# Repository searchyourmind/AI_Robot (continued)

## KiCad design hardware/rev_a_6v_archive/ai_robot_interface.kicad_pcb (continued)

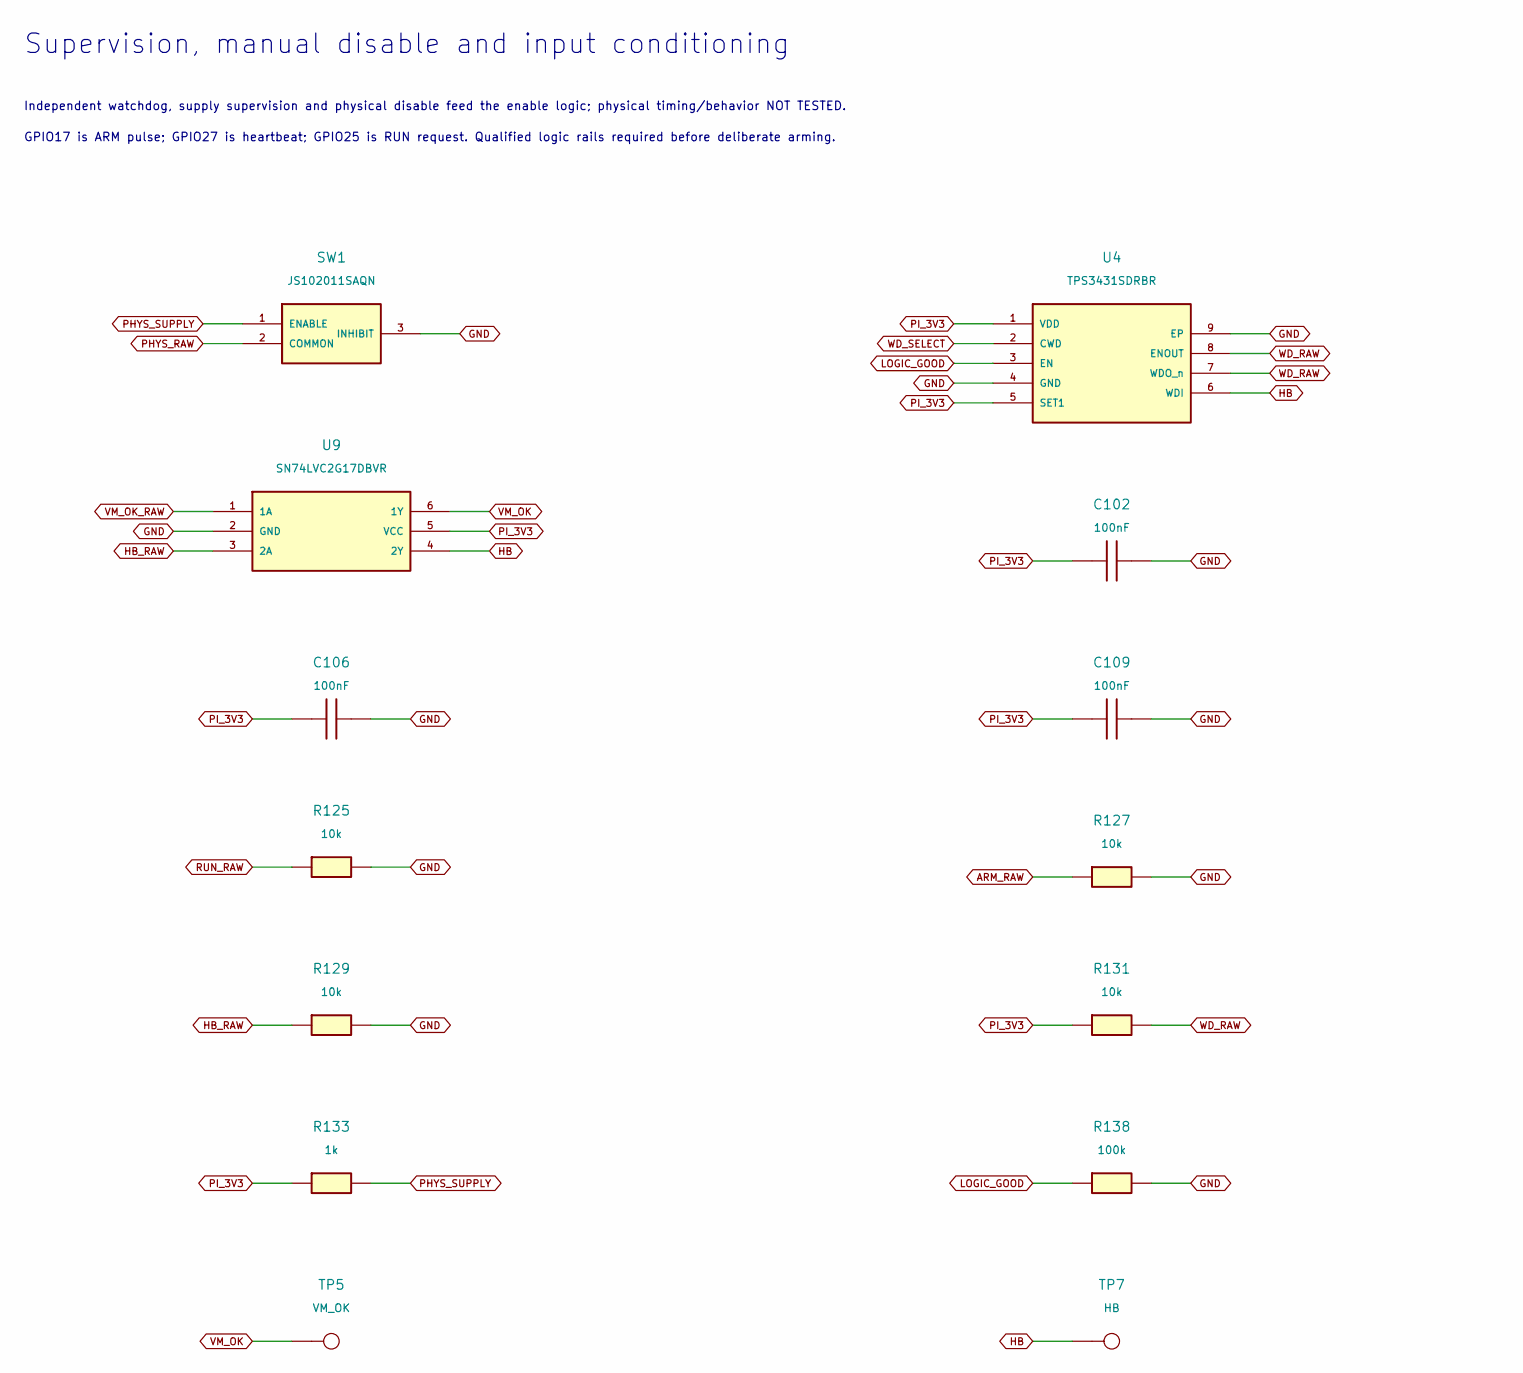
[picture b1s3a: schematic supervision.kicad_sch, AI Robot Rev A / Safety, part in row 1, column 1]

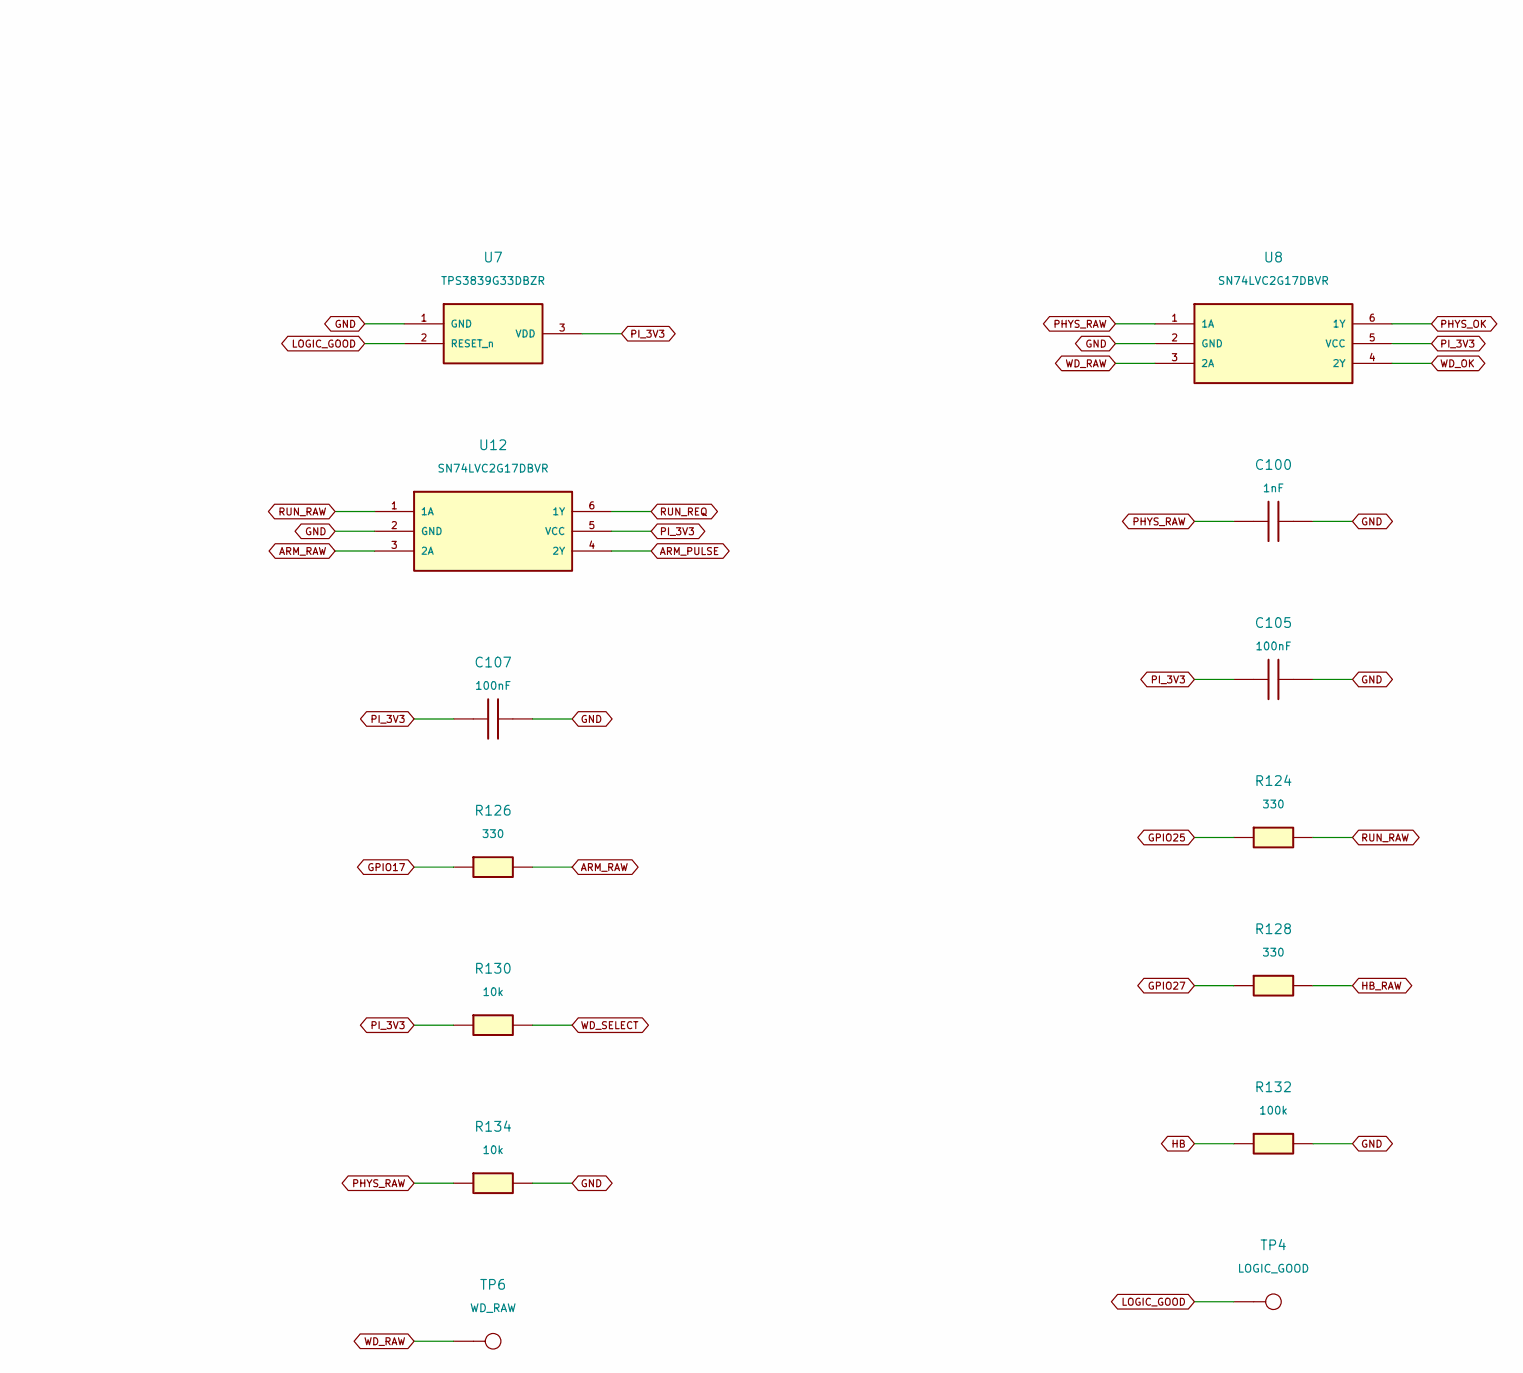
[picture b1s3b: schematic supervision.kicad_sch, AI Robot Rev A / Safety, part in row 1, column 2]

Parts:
C100: 1nF; C_0603_1608Metric; MPN GRM1885C1H102JA01D
C102, C105, C106, C107, C109: 100nF; C_0603_1608Metric; MPN CC0603KRX7R9BB104
R124, R126, R128: 330; R_0603_1608Metric; MPN RC0603FR-07330RL
R125, R127, R129, R130, R131, R134: 10k; R_0603_1608Metric; MPN RC0603FR-0710KL
R132, R138: 100k; R_0603_1608Metric; MPN RC0603FR-07100KL
R133: 1k; R_0603_1608Metric; MPN RC0603FR-071KL
SW1: JS102011SAQN; SW_SPDT_CK_JS102011SAQN; MPN JS102011SAQN
TP4: LOGIC_GOOD; TestPoint_Pad_D1.5mm; MPN PCB_COPPER_FEATURE
TP5: VM_OK; TestPoint_Pad_D1.5mm; MPN PCB_COPPER_FEATURE
TP6: WD_RAW; TestPoint_Pad_D1.5mm; MPN PCB_COPPER_FEATURE
TP7: HB; TestPoint_Pad_D1.5mm; MPN PCB_COPPER_FEATURE
U4: TPS3431SDRBR; TPS3431_DRB8_3x3_P0.65; MPN TPS3431SDRBR
U7: TPS3839G33DBZR; SOT-23; MPN TPS3839G33DBZR
U8, U9, U12: SN74LVC2G17DBVR; SOT-23-6; MPN SN74LVC2G17DBVR

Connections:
ARM_PULSE: U12.4 (2Y); also elsewhere on the board
ARM_RAW: R126.2, R127.1, U12.3 (2A)
GND: C100.2, C102.2, C105.2, C106.2, C107.2, C109.2, R125.2, R127.2, R129.2, R132.2, R134.2, R138.2, SW1.3 (INHIBIT), U4.4 (GND), U4.9 (EP), U7.1 (GND), U8.2 (GND), U9.2 (GND), U12.2 (GND); also elsewhere on the board
GPIO17: R126.1; also elsewhere on the board
GPIO25: R124.1; also elsewhere on the board
GPIO27: R128.1; also elsewhere on the board
HB: R132.1, TP7.1, U4.6 (WDI), U9.4 (2Y)
HB_RAW: R128.2, R129.1, U9.3 (2A)
LOGIC_GOOD: R138.1, TP4.1, U4.3 (EN), U7.2 (RESET_n); also elsewhere on the board
PHYS_OK: U8.6 (1Y); also elsewhere on the board
PHYS_RAW: C100.1, R134.1, SW1.2 (COMMON), U8.1 (1A)
PHYS_SUPPLY: R133.2, SW1.1 (ENABLE)
PI_3V3: C102.1, C105.1, C106.1, C107.1, C109.1, R130.1, R131.1, R133.1, U4.1 (VDD), U4.5 (SET1), U7.3 (VDD), U8.5 (VCC), U9.5 (VCC), U12.5 (VCC); also elsewhere on the board
RUN_RAW: R124.2, R125.1, U12.1 (1A)
RUN_REQ: U12.6 (1Y); also elsewhere on the board
VM_OK: TP5.1, U9.6 (1Y); also elsewhere on the board
VM_OK_RAW: U9.1 (1A); also elsewhere on the board
WD_OK: U8.4 (2Y); also elsewhere on the board
WD_RAW: R131.2, TP6.1, U4.7 (WDO_n), U4.8 (ENOUT), U8.3 (2A)
WD_SELECT: R130.2, U4.2 (CWD)

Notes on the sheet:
Supervision, manual disable and input conditioning
Independent watchdog, supply supervision and physical disable feed the enable logic; physical timing/behavior NOT TESTED.
GPIO17 is ARM pulse; GPIO27 is heartbeat; GPIO25 is RUN request. Qualified logic rails required before deliberate arming.

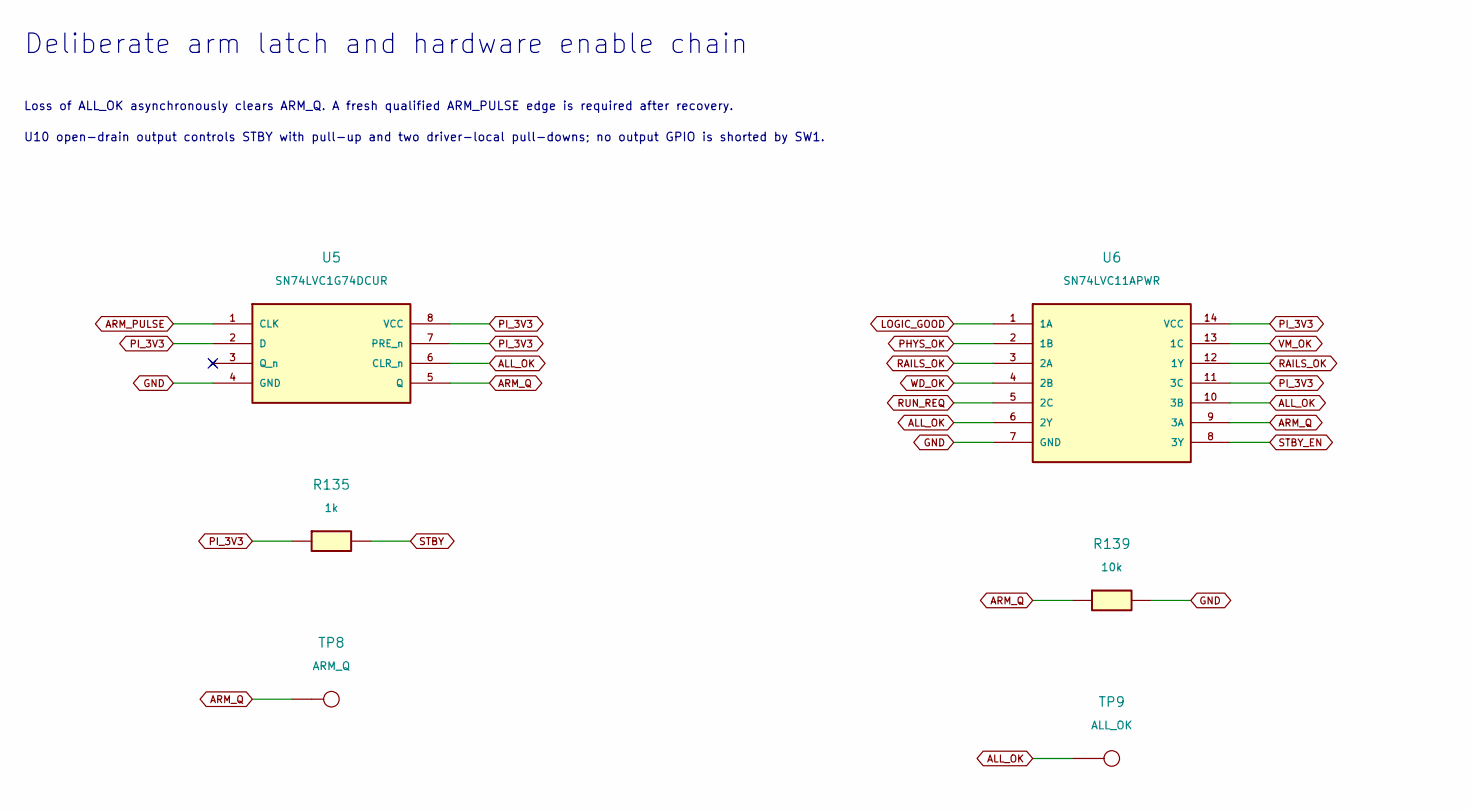
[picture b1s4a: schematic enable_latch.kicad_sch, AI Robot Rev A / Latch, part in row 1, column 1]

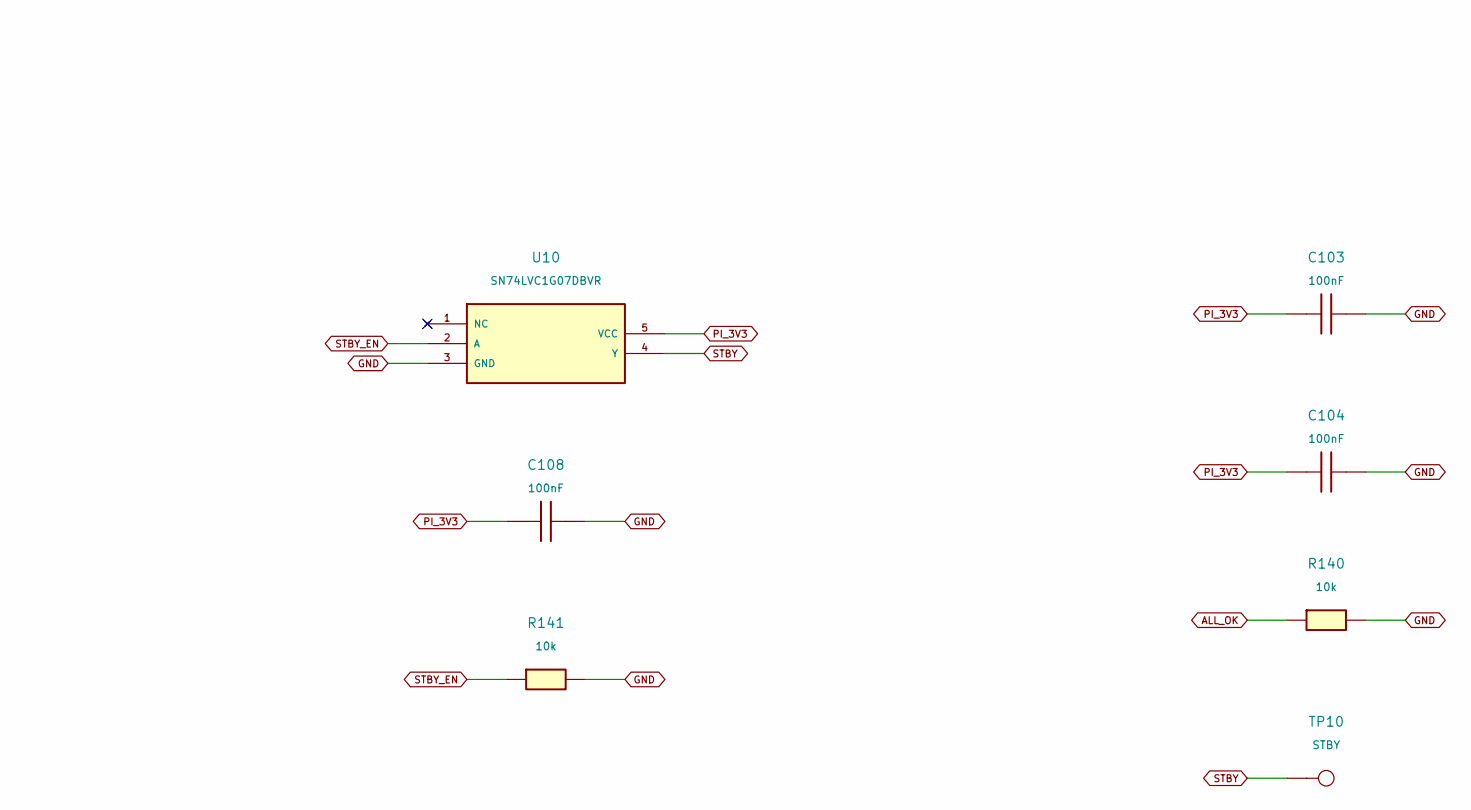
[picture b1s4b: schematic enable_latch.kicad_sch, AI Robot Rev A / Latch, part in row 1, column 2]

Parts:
C103, C104, C108: 100nF; C_0603_1608Metric; MPN CC0603KRX7R9BB104
R135: 1k; R_0603_1608Metric; MPN RC0603FR-071KL
R139, R140, R141: 10k; R_0603_1608Metric; MPN RC0603FR-0710KL
TP8: ARM_Q; TestPoint_Pad_D1.5mm; MPN PCB_COPPER_FEATURE
TP9: ALL_OK; TestPoint_Pad_D1.5mm; MPN PCB_COPPER_FEATURE
TP10: STBY; TestPoint_Pad_D1.5mm; MPN PCB_COPPER_FEATURE
U5: SN74LVC1G74DCUR; TI_DCU0008A; MPN SN74LVC1G74DCUR
U6: SN74LVC11APWR; TSSOP-14_4.4x5mm_P0.65mm; MPN SN74LVC11APWR
U10: SN74LVC1G07DBVR; SOT-23-5; MPN SN74LVC1G07DBVR

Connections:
ALL_OK: R140.1, TP9.1, U5.6 (CLR_n), U6.6 (2Y), U6.10 (3B)
ARM_PULSE: U5.1 (CLK); also elsewhere on the board
ARM_Q: R139.1, TP8.1, U5.5 (Q), U6.9 (3A)
GND: C103.2, C104.2, C108.2, R139.2, R140.2, R141.2, U5.4 (GND), U6.7 (GND), U10.3 (GND); also elsewhere on the board
LOGIC_GOOD: U6.1 (1A); also elsewhere on the board
PHYS_OK: U6.2 (1B); also elsewhere on the board
PI_3V3: C103.1, C104.1, C108.1, R135.1, U5.2 (D), U5.7 (PRE_n), U5.8 (VCC), U6.11 (3C), U6.14 (VCC), U10.5 (VCC); also elsewhere on the board
RAILS_OK: U6.3 (2A), U6.12 (1Y)
RUN_REQ: U6.5 (2C); also elsewhere on the board
STBY: R135.2, TP10.1, U10.4 (Y); also elsewhere on the board
STBY_EN: R141.1, U6.8 (3Y), U10.2 (A)
VM_OK: U6.13 (1C); also elsewhere on the board
WD_OK: U6.4 (2B); also elsewhere on the board

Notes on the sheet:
Deliberate arm latch and hardware enable chain
Loss of ALL_OK asynchronously clears ARM_Q. A fresh qualified ARM_PULSE edge is required after recovery.
U10 open-drain output controls STBY with pull-up and two driver-local pull-downs; no output GPIO is shorted by SW1.

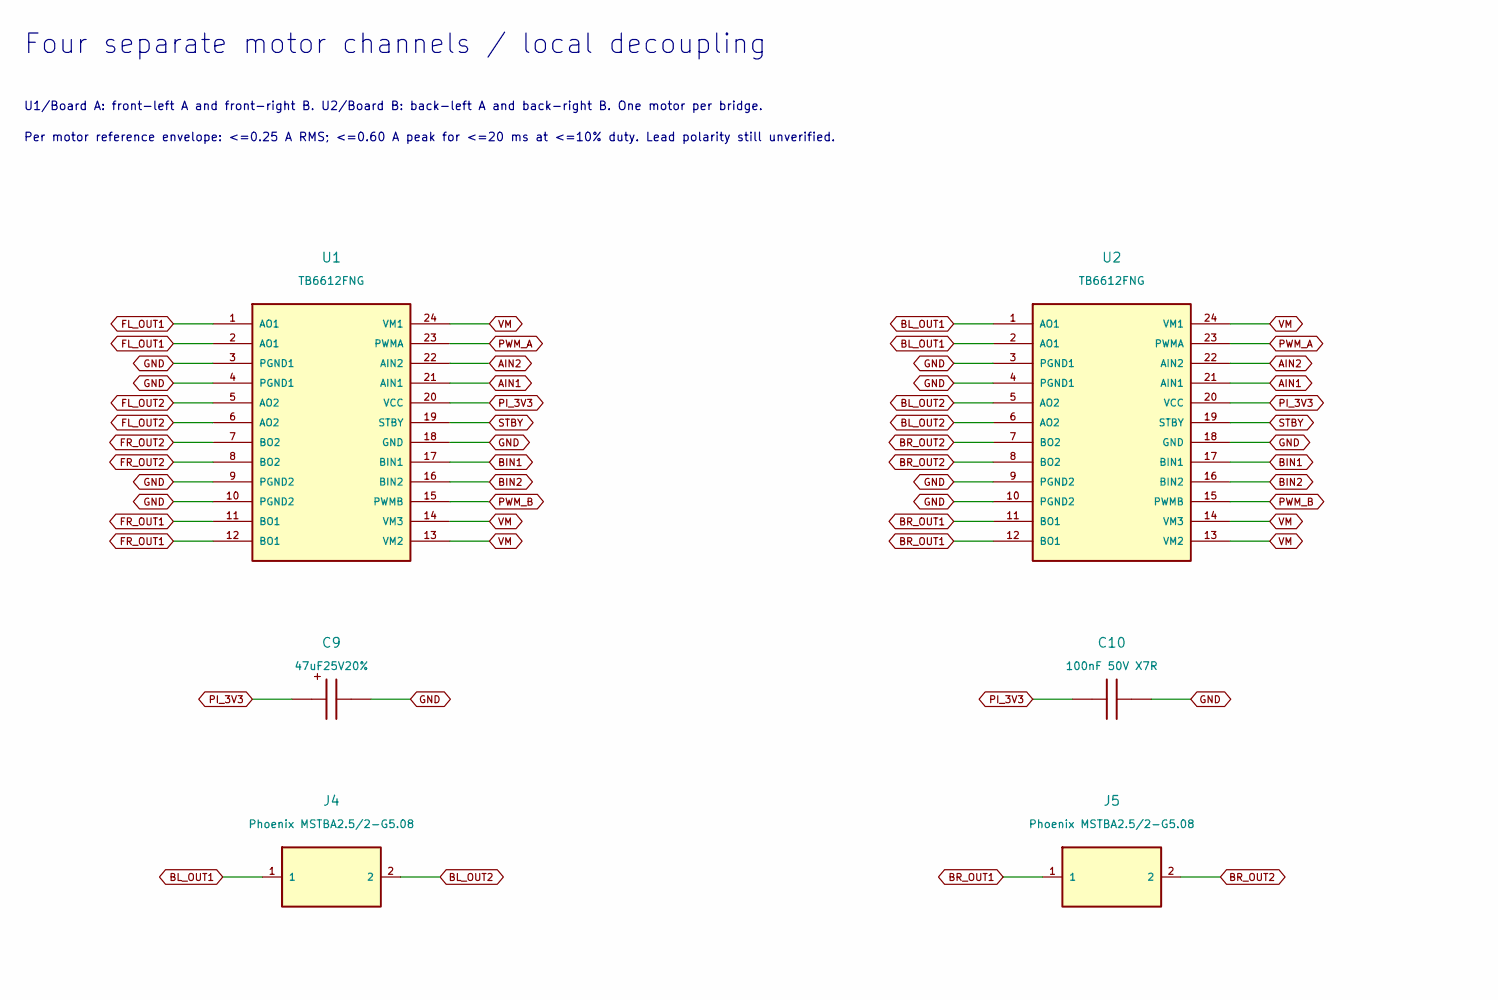
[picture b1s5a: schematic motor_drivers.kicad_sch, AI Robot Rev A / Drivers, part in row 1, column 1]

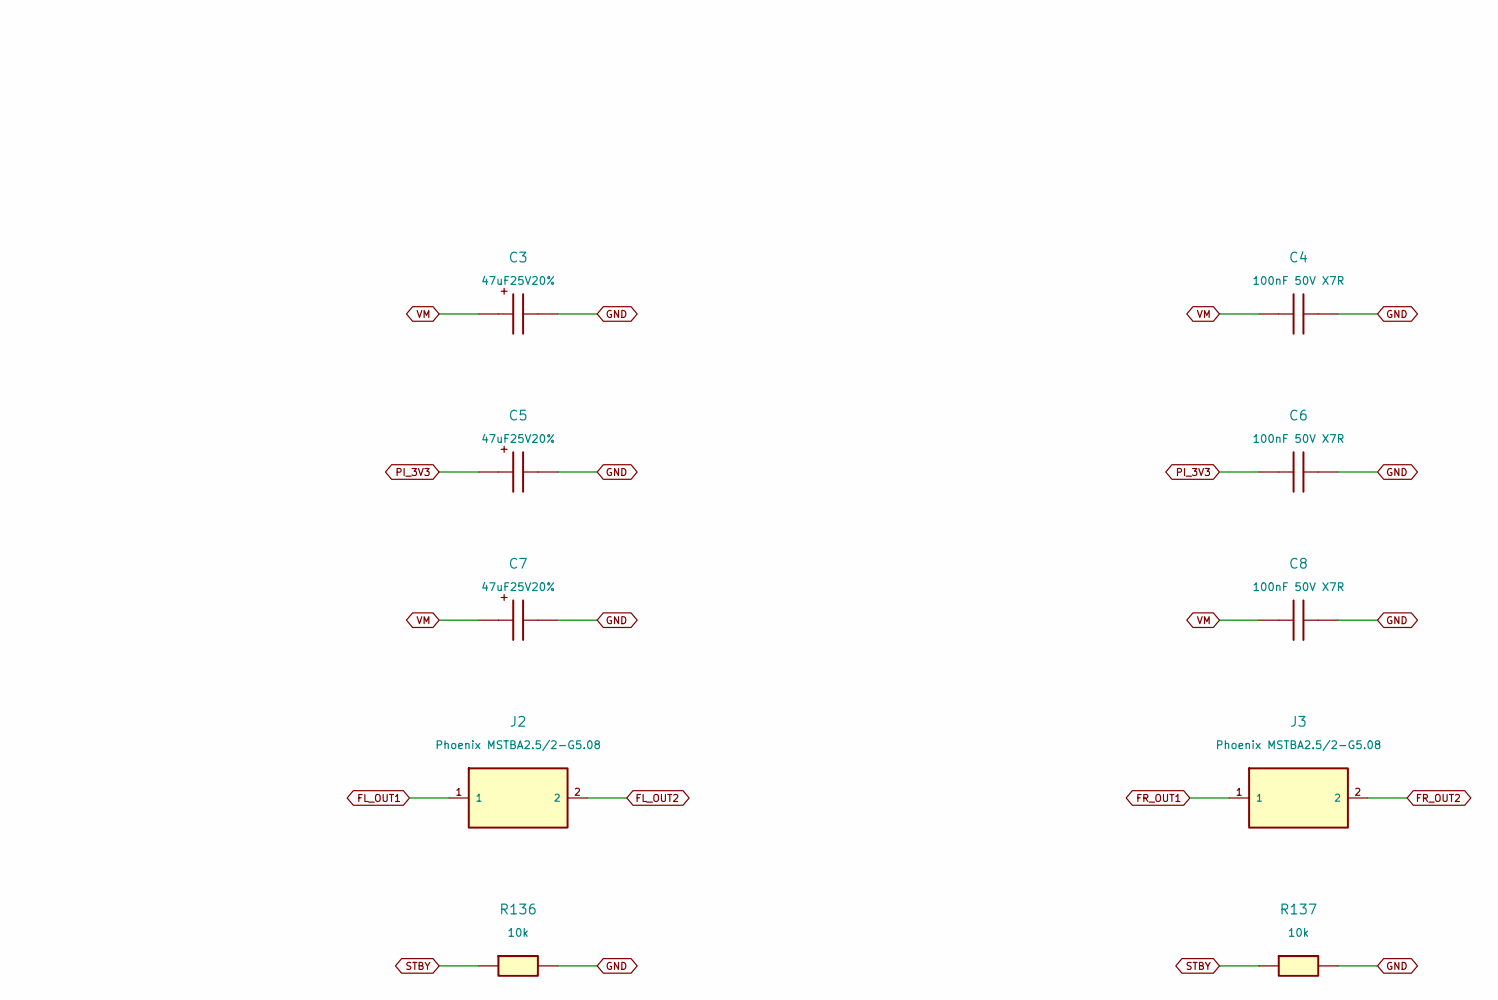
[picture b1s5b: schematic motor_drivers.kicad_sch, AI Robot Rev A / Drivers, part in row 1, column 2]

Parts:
C3, C5, C7, C9: 47uF25V20%; CP_Radial_D5.0mm_P2.00mm; MPN EEUFR1E470
C4, C6, C8, C10: 100nF 50V X7R; C_0805_2012Metric; MPN C0805C104K5RACTU
J2, J3, J4, J5: Phoenix MSTBA2.5/2-G5.08; PhoenixContact_MSTBA_2,5_2-G-5,08_1x02_P5.08mm_Horizontal; MPN 1757242
R136, R137: 10k; R_0603_1608Metric; MPN RC0603FR-0710KL
U1, U2: TB6612FNG; TB6612FNG_SSOP24_5.6x7.8_P0.65; MPN TB6612FNG(O,C,8,EL

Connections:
AIN1: U1.21 (AIN1), U2.21 (AIN1); also elsewhere on the board
AIN2: U1.22 (AIN2), U2.22 (AIN2); also elsewhere on the board
BIN1: U1.17 (BIN1), U2.17 (BIN1); also elsewhere on the board
BIN2: U1.16 (BIN2), U2.16 (BIN2); also elsewhere on the board
BL_OUT1: J4.1, U2.1 (AO1), U2.2 (AO1)
BL_OUT2: J4.2, U2.5 (AO2), U2.6 (AO2)
BR_OUT1: J5.1, U2.11 (BO1), U2.12 (BO1)
BR_OUT2: J5.2, U2.7 (BO2), U2.8 (BO2)
FL_OUT1: J2.1, U1.1 (AO1), U1.2 (AO1)
FL_OUT2: J2.2, U1.5 (AO2), U1.6 (AO2)
FR_OUT1: J3.1, U1.11 (BO1), U1.12 (BO1)
FR_OUT2: J3.2, U1.7 (BO2), U1.8 (BO2)
GND: C3.2, C4.2, C5.2, C6.2, C7.2, C8.2, C9.2, C10.2, R136.2, R137.2, U1.3 (PGND1), U1.4 (PGND1), U1.9 (PGND2), U1.10 (PGND2), U1.18 (GND), U2.3 (PGND1), U2.4 (PGND1), U2.9 (PGND2), U2.10 (PGND2), U2.18 (GND); also elsewhere on the board
PI_3V3: C5.1, C6.1, C9.1, C10.1, U1.20 (VCC), U2.20 (VCC); also elsewhere on the board
PWM_A: U1.23 (PWMA), U2.23 (PWMA); also elsewhere on the board
PWM_B: U1.15 (PWMB), U2.15 (PWMB); also elsewhere on the board
STBY: R136.1, R137.1, U1.19 (STBY), U2.19 (STBY); also elsewhere on the board
VM: C3.1, C4.1, C7.1, C8.1, U1.13 (VM2), U1.14 (VM3), U1.24 (VM1), U2.13 (VM2), U2.14 (VM3), U2.24 (VM1); also elsewhere on the board

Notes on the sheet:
Four separate motor channels / local decoupling
U1/Board A: front-left A and front-right B. U2/Board B: back-left A and back-right B. One motor per bridge.
Per motor reference envelope: <=0.25 A RMS; <=0.60 A peak for <=20 ms at <=10% duty. Lead polarity still unverified.

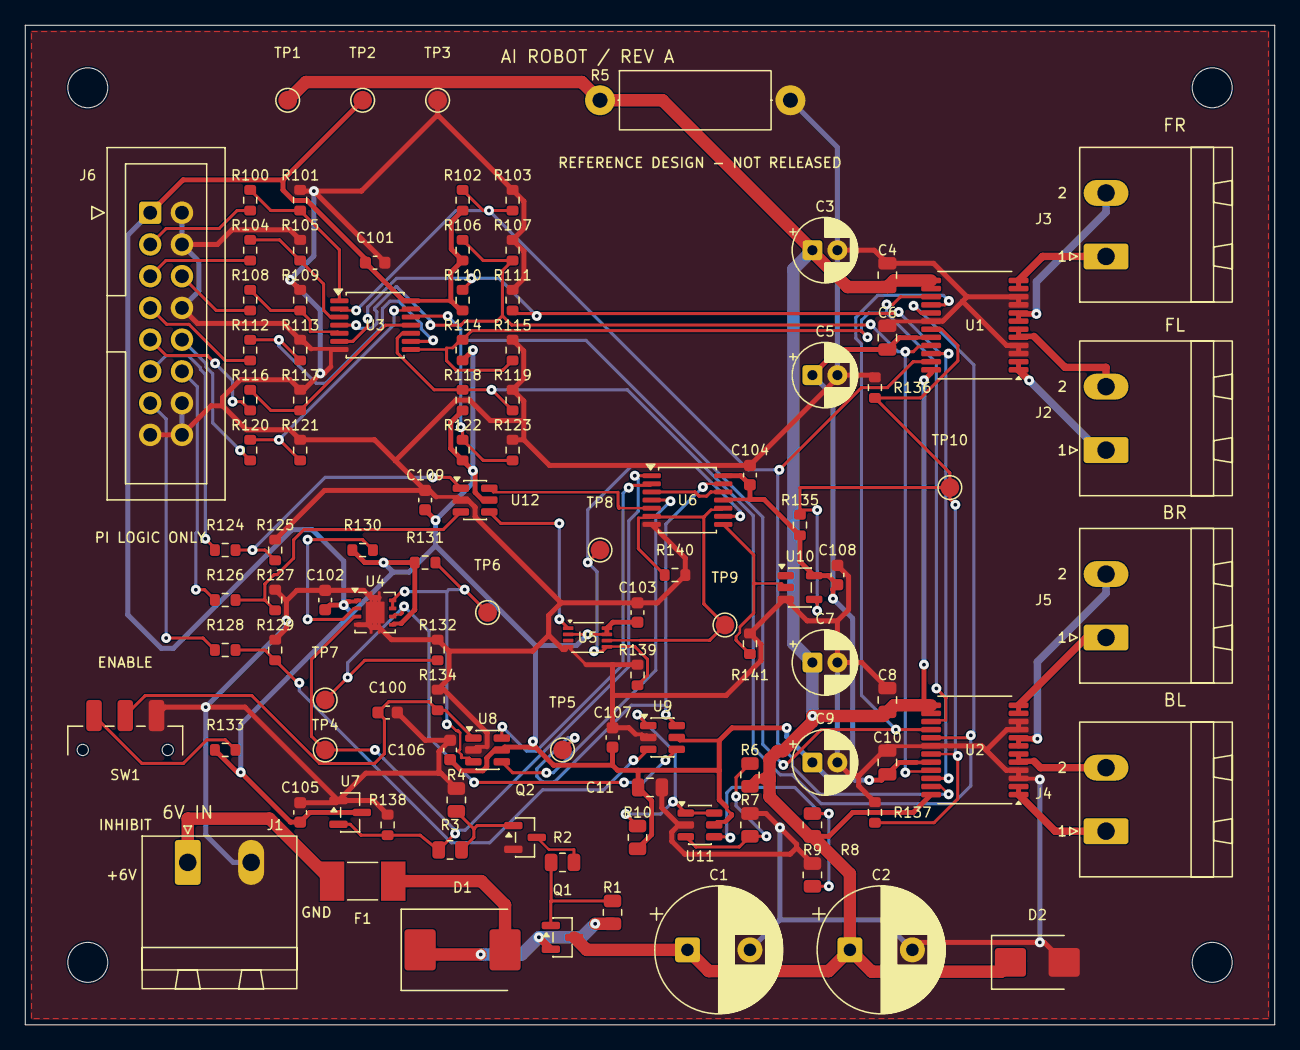
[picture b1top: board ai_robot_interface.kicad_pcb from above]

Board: 2 copper layers, 100.0 x 80.0 mm, 111 parts (0 on the bottom side), 60 nets.

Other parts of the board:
H1, H2, H3, H4: M3 NPTH; MountingHole_3.2mm_M3

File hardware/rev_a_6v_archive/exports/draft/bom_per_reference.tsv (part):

Status	References	Quantity_per_board	Manufacturer	MPN	Value	Footprint	Mount	Source_URL	Notes
DRAFT - NOT RELEASED FOR FABRICATION	C1	1	Panasonic	EEUFR1E102	1000uF25V20%	Capacitor_THT:CP_Radial_D10.0mm_P5.00mm	THT	https://industrial.panasonic.com/ww/products/pt/aluminum-cap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	1000 uF; 25 V; 20%; radial D10 x L20 mm; P5 mm
DRAFT - NOT RELEASED FOR FABRICATION	C2	1	Panasonic	EEUFR1E102	1000uF25V20%	Capacitor_THT:CP_Radial_D10.0mm_P5.00mm	THT	https://industrial.panasonic.com/ww/products/pt/aluminum-cap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	1000 uF; 25 V; 20%; radial D10 x L20 mm; P5 mm
DRAFT - NOT RELEASED FOR FABRICATION	C3	1	Panasonic	EEUFR1E470	47uF25V20%	Capacitor_THT:CP_Radial_D5.0mm_P2.00mm	THT	https://industrial.panasonic.com/ww/products/pt/aluminum-cap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	47 uF; 25 V; 20%; radial D5 x L11 mm; P2 mm
DRAFT - NOT RELEASED FOR FABRICATION	C4	1	KEMET	C0805C104K5RACTU	100nF 50V X7R	Capacitor_SMD:C_0805_2012Metric	SMD	https://search.kemet.com/download/specsheet/C0805C104K5RACTU	100 nF; 50 V; X7R; 10%; 0805
DRAFT - NOT RELEASED FOR FABRICATION	C5	1	Panasonic	EEUFR1E470	47uF25V20%	Capacitor_THT:CP_Radial_D5.0mm_P2.00mm	THT	https://industrial.panasonic.com/ww/products/pt/aluminum-cap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	47 uF; 25 V; 20%; radial D5 x L11 mm; P2 mm
DRAFT - NOT RELEASED FOR FABRICATION	C6	1	KEMET	C0805C104K5RACTU	100nF 50V X7R	Capacitor_SMD:C_0805_2012Metric	SMD	https://search.kemet.com/download/specsheet/C0805C104K5RACTU	100 nF; 50 V; X7R; 10%; 0805
DRAFT - NOT RELEASED FOR FABRICATION	C7	1	Panasonic	EEUFR1E470	47uF25V20%	Capacitor_THT:CP_Radial_D5.0mm_P2.00mm	THT	https://industrial.panasonic.com/ww/products/pt/aluminum-cap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	47 uF; 25 V; 20%; radial D5 x L11 mm; P2 mm
DRAFT - NOT RELEASED FOR FABRICATION	C8	1	KEMET	C0805C104K5RACTU	100nF 50V X7R	Capacitor_SMD:C_0805_2012Metric	SMD	https://search.kemet.com/download/specsheet/C0805C104K5RACTU	100 nF; 50 V; X7R; 10%; 0805
DRAFT - NOT RELEASED FOR FABRICATION	C9	1	Panasonic	EEUFR1E470	47uF25V20%	Capacitor_THT:CP_Radial_D5.0mm_P2.00mm	THT	https://industrial.panasonic.com/ww/products/pt/aluminum-cap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	47 uF; 25 V; 20%; radial D5 x L11 mm; P2 mm
DRAFT - NOT RELEASED FOR FABRICATION	C10	1	KEMET	C0805C104K5RACTU	100nF 50V X7R	Capacitor_SMD:C_0805_2012Metric	SMD	https://search.kemet.com/download/specsheet/C0805C104K5RACTU	100 nF; 50 V; X7R; 10%; 0805
DRAFT - NOT RELEASED FOR FABRICATION	C11	1	KEMET	C0805C104K5RACTU	100nF 50V X7R	Capacitor_SMD:C_0805_2012Metric	SMD	https://search.kemet.com/download/specsheet/C0805C104K5RACTU	100 nF; 50 V; X7R; 10%; 0805
DRAFT - NOT RELEASED FOR FABRICATION	C100	1	Murata	GRM1885C1H102JA01D	1nF	Capacitor_SMD:C_0603_1608Metric	SMD	https://datasheet.octopart.com/GRM1885C1H102JA01D-Murata-dat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	Manufacturer-authored archived datasheet; direct manufacturer retrieval unavailable; refresh before procurement; 1 nF; C0G; 50 V; 5%; 0603
DRAFT - NOT RELEASED FOR FABRICATION	C101	1	YAGEO	CC0603KRX7R9BB104	100nF	Capacitor_SMD:C_0603_1608Metric	SMD	https://yageogroup.com/download/specsheet/CC0603KRX7R9BB104	100 nF; 50 V; X7R; 10%; 0603
DRAFT - NOT RELEASED FOR FABRICATION	C102	1	YAGEO	CC0603KRX7R9BB104	100nF	Capacitor_SMD:C_0603_1608Metric	SMD	https://yageogroup.com/download/specsheet/CC0603KRX7R9BB104	100 nF; 50 V; X7R; 10%; 0603
DRAFT - NOT RELEASED FOR FABRICATION	C103	1	YAGEO	CC0603KRX7R9BB104	100nF	Capacitor_SMD:C_0603_1608Metric	SMD	https://yageogroup.com/download/specsheet/CC0603KRX7R9BB104	100 nF; 50 V; X7R; 10%; 0603
DRAFT - NOT RELEASED FOR FABRICATION	C104	1	YAGEO	CC0603KRX7R9BB104	100nF	Capacitor_SMD:C_0603_1608Metric	SMD	https://yageogroup.com/download/specsheet/CC0603KRX7R9BB104	100 nF; 50 V; X7R; 10%; 0603
DRAFT - NOT RELEASED FOR FABRICATION	C105	1	YAGEO	CC0603KRX7R9BB104	100nF	Capacitor_SMD:C_0603_1608Metric	SMD	https://yageogroup.com/download/specsheet/CC0603KRX7R9BB104	100 nF; 50 V; X7R; 10%; 0603
DRAFT - NOT RELEASED FOR FABRICATION	C106	1	YAGEO	CC0603KRX7R9BB104	100nF	Capacitor_SMD:C_0603_1608Metric	SMD	https://yageogroup.com/download/specsheet/CC0603KRX7R9BB104	100 nF; 50 V; X7R; 10%; 0603
DRAFT - NOT RELEASED FOR FABRICATION	C107	1	YAGEO	CC0603KRX7R9BB104	100nF	Capacitor_SMD:C_0603_1608Metric	SMD	https://yageogroup.com/download/specsheet/CC0603KRX7R9BB104	100 nF; 50 V; X7R; 10%; 0603
DRAFT - NOT RELEASED FOR FABRICATION	C108	1	YAGEO	CC0603KRX7R9BB104	100nF	Capacitor_SMD:C_0603_1608Metric	SMD	https://yageogroup.com/download/specsheet/CC0603KRX7R9BB104	100 nF; 50 V; X7R; 10%; 0603
DRAFT - NOT RELEASED FOR FABRICATION	C109	1	YAGEO	CC0603KRX7R9BB104	100nF	Capacitor_SMD:C_0603_1608Metric	SMD	https://yageogroup.com/download/specsheet/CC0603KRX7R9BB104	100 nF; 50 V; X7R; 10%; 0603
DRAFT - NOT RELEASED FOR FABRICATION	D1	1	Vishay	SSC54-E3/57T	40V 5A	Diode_SMD:D_SMC	SMD	https://www.vishay.com/docs/88885/ssc53l.pdf	SMC; cathode band to REV_PROTECTED
DRAFT - NOT RELEASED FOR FABRICATION	D2	1	Littelfuse	SMBJ7.0A	7V unidirectional	Diode_SMD:D_SMB	SMD	https://www.littelfuse.com/assetdocs/tvs-diodes-smbj-series-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	Unidirectional; cathode band to VM
DRAFT - NOT RELEASED FOR FABRICATION	F1	1	Littelfuse	0451002.MRL	2A 125V	AI_Robot:Fuse_Littelfuse_451	SMD	https://www.littelfuse.com/assetdocs/fuse-451-and-453-datash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	2 A; non-resettable; not a per-channel current limiter
DRAFT - NOT RELEASED FOR FABRICATION	J1	1	Phoenix Contact	1757242	Phoenix MSTBA2.5/2-G5.08	Connector_Phoenix_MSTB:PhoenixContact_MSTBA_2,5_2-G-5,08_1x02_P5.08mm_Horizontal	THT	https://www.phoenixcontact.com/en-de/products/pcb-header-mst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	Board header only; off-board mating plug 1757019 listed separately
DRAFT - NOT RELEASED FOR FABRICATION	J2	1	Phoenix Contact	1757242	Phoenix MSTBA2.5/2-G5.08	Connector_Phoenix_MSTB:PhoenixContact_MSTBA_2,5_2-G-5,08_1x02_P5.08mm_Horizontal	THT	https://www.phoenixcontact.com/en-de/products/pcb-header-mst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	Board header only; off-board mating plug 1757019 listed separately
DRAFT - NOT RELEASED FOR FABRICATION	J3	1	Phoenix Contact	1757242	Phoenix MSTBA2.5/2-G5.08	Connector_Phoenix_MSTB:PhoenixContact_MSTBA_2,5_2-G-5,08_1x02_P5.08mm_Horizontal	THT	https://www.phoenixcontact.com/en-de/products/pcb-header-mst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	Board header only; off-board mating plug 1757019 listed separately
DRAFT - NOT RELEASED FOR FABRICATION	J4	1	Phoenix Contact	1757242	Phoenix MSTBA2.5/2-G5.08	Connector_Phoenix_MSTB:PhoenixContact_MSTBA_2,5_2-G-5,08_1x02_P5.08mm_Horizontal	THT	https://www.phoenixcontact.com/en-de/products/pcb-header-mst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	Board header only; off-board mating plug 1757019 listed separately
DRAFT - NOT RELEASED FOR FABRICATION	J5	1	Phoenix Contact	1757242	Phoenix MSTBA2.5/2-G5.08	Connector_Phoenix_MSTB:PhoenixContact_MSTBA_2,5_2-G-5,08_1x02_P5.08mm_Horizontal	THT	https://www.phoenixcontact.com/en-de/products/pcb-header-mst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	Board header only; off-board mating plug 1757019 listed separately
DRAFT - NOT RELEASED FOR FABRICATION	J6	1	Wurth Elektronik	61201621621	Pi logic / IDC16	AI_Robot:IDC_Wurth_61201621621	THT	https://www.we-online.com/components/products/datasheet/6120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	Shrouded 16-pin logic header; custom project footprint; not Pi 40-pin compatible
DRAFT - NOT RELEASED FOR FABRICATION	Q1	1	Alpha & Omega Semiconductor	AO3401A	-30V P-MOS	Package_TO_SOT_SMD:SOT-23	SMD	https://www.aosmd.com/pdfs/datasheet/AO3401A.pdf	SOT-23; pin1 G, pin2 S, pin3 D
DRAFT - NOT RELEASED FOR FABRICATION	Q2	1	onsemi	MMBT3904LT1G	40V NPN	Package_TO_SOT_SMD:SOT-23	SMD	https://www.onsemi.com/pdf/datasheet/mmbt3904lt1-d.pdf	SOT-23; pin1 B, pin2 E, pin3 C
DRAFT - NOT RELEASED FOR FABRICATION	R1	1	Vishay	TNPW080522K0BEEA	22k 0.1% 25ppm/K	Resistor_SMD:R_0805_2012Metric	SMD	https://www.vishay.com/docs/28758/tnpw_e3.pdf	Full manufacturer ordering code; 0805; 0.1%; 25 ppm/K
DRAFT - NOT RELEASED FOR FABRICATION	R2	1	Vishay	TNPW08054K70BEEA	4.7k 0.1% 25ppm/K	Resistor_SMD:R_0805_2012Metric	SMD	https://www.vishay.com/docs/28758/tnpw_e3.pdf	Full manufacturer ordering code; 0805; 0.1%; 25 ppm/K
DRAFT - NOT RELEASED FOR FABRICATION	R3	1	Vishay	TNPW080510K0BEEA	10k 0.1% 25ppm/K	Resistor_SMD:R_0805_2012Metric	SMD	https://www.vishay.com/docs/28758/tnpw_e3.pdf	Full manufacturer ordering code; 0805; 0.1%; 25 ppm/K
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
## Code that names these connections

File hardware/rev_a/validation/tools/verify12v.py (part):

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        required('R46',{1:'EFUSE_PG_SENSE',2:'GND'})
        required('R11',{1:'FEED_ENABLE',2:'EFUSE_SHDN'})
        required('R12',{1:'EFUSE_SHDN',2:'GND'})
        required('J6',{1:'PI_3V3',2:'GND',3:'GPIO18',4:'GND',5:'GPIO23',6:None,7:'GPIO13',8:'GND',9:'GPIO5',10:None,11:'GPIO25',12:'GPIO17',13:'GPIO27',14:'GND',15:'GND',16:'GND'})
        for ref,wheel,left in [('U20','FL',True),('U21','FR',False),('U22','BL',True),('U23','BR',False)]:
            side='LEFT' if left else 'RIGHT'
            required(ref,{1:side+'_IN1',2:side+'_IN2',3:'FEED_ENABLE',4:'FAULT_OK_RAW',5:wheel+'_VREF',6:wheel+'_IPROPI',7:None,8:wheel+'_OUT1',9:'GND',10:wheel+'_OUT2',11:'VM',12:wheel+'_VCP',13:wheel+'_CPH',14:wheel+'_CPL',15:'GND',16:'PI_3V3',17:'GND'})
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
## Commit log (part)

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2026-02-01 Add root README
